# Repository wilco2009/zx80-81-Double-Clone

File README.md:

# PROJECT DOUBLE CLON ZX80/ZX81

Reading the works of [Grant Searle](http://searle.x10host.com/#ZX80), I have decided to start with the project to build a full computer to understand in depth his functionality. What can be more proper that a ZX80 totally based in discrete chips? 

In my spare time, I have started to work on it and you can find the results in the following lines.

I have copyied the schematics from the original zx80, and have made some modifications on it.

- I have added the extra circuitery to generate /NMI signal (Grant Searle Schematics), making possible to have two machines in one, by selecting it through a switch.
- Original 1K RAM in two chips have been replaced by one SRAM chip of  32KB.
- Original 4K ROM have been replaced by a EEPROM of 32KB. It necesary to store both ROMs (ZX80/ZX81) and it is cheaper than other smaller EPROMs.
-  RF modulator have been removed and replaced by a circuit to generate the standard back porch, missing in the original ZX80 PAL signal.

The final result is nor a exact copy of the original as the case of Grant, but the board match accurately in the original case, and I very happy with the result.

## TECHNICAL & ASSEMBLY INFORMATION

In this project you can find the necesary information to build your own zx80. I think the most funny way to obtain your clon is to do it from zero, but if you wanna a clon and need the PCB or you have not enough knowledge or experience to assembly it, I have some spare PCBs and componentes, and I can sell them or assembly the clon for you. Please feel free to contact me and I'm sure we can reach an agreenment. ;)

Current version: 1.1

![](https://lh3.googleusercontent.com/rCJV6tn4bRtD5xP2J01XtbQhOAFcQkIHwjG2PTs5kUFLTJYEPpwRD9dPU9Wus_7P2roRMrFiV_r6bx4AB1eH3hhHG4VBcHm-jtsIfwT51LC9u5qDKVhMcgAC-uYpSRKtiEv6ICVfqDUmrft0VXdILqsLhS6f-ci5W7Umk74fWQYKdmCltZMjROodQSZJIWuj3sWZtwkx2SUn3Zm80keVlYFTvZAvUO4RSQdXKRYVVGPSJaJdWytPF-uEiMIzvv5qfT4mYDBnC-GfqofApX20-UyLoEvZvTxQKA6cM-wEbGhz7QX-2P5Ngz30T_aOOOsLFDybzaFVSkEu0-Aztuu-lsrUIOo-5BsEfMnfYWue9epBj3OxYwocKKNFXdKxPxSTB5UOF6xXgVXRRxUQgXtDaMdEkAA_8DmF7i70zOS1lgH9-kZtPJs_eu8M_NfuGdDXssUw_kXJS4aPKvZ8_ZMPcppX3AiGHYtJN76VHx3QsB8ZefL5xlYTNOjEyXqZktvqzpaWWwEC28iiI7Rkx7_iQb64YHFRn1RQnPd6H6iP8zeCWNG2FOciLwMQ_T2f79s7PXthGdRW-6iFVxDD1xcBhBEmMfMiO6Gdjo2rIUpM3x4K8OVurMoqewDZ2G1iEkNCWaOpOh4981G3RFsP8XLy4C4ls8FTX44saukjyuqq=w845-h981-no)

## JUMPER POSITION
JP1: RAMOE, Not relevant but must be present in one position
JP2:
              1-2 - Inverse Video
              2-3 - Standard Video
S2: ZX80/81 Mode selection (If you use external selection from the expansion board this jumper have to be removed)
              1-2 - ZX81 mode
              2-3 - ZX80 mode.

S4: Function of the Pin23B in the expansion bus. 
In original ZX80 pin 23B of the expansion bus is spare, but in a ZX81 PIN23B is use as /ROMCS signal.
If you want to use external zx81 mode selection form the expansion board you have to use position 1-2. In this case (in zx81 mode) cards replacing the internal ROM will not works.
If you prefer to use this kind of cards, you have to wire the zx81 selector (S2) directly to an accesible switch and set S4 in 2-3 position (remember to remove JP1 in the expansion board)
              1-2 - ZX81/ZX80 mode selection in PIN 23B
              2-3 - /ROMOE in PIN 23B

### Back porch Grant Searle solution:

              JP3 = 2-3
              JP5 = OFF
              JP6 = 1-2

### Back porch generation José Leandro solution:
              Adjust image with R37 & R33
              JP3 = 1-2
              JP5 = ON
              JP6 = 2-3

### Without Backporch generation (original ZX80 video)
              JP3 = 1-2
              JP5 = OFF
              JP6 = 1-2
              
## EXPANSION BOARD

This board has double functionality, first leaves enough room to connect zx81 cards  without trip with the video connector, and by other hand adds some extra functionality to the main board.

Expansion board let you to supply power to the computer with a miniUSB charger. If you plan to use external cards using 9V you will must to connect the computer to a 9V PS through the standard conector.
If you use the miniUSB supply, you could use the ON/OFF switch present in the board (S1) to turn on the computer.
S2 is a reset button, and it will works in any case.
JP7 Lets you to select ZX80/81 mode from the board if the position of the main jumper S4 is 1-2 and JP1 in the expansion board is ON.

JP1 Lets you aisle pin23B in the computer from the JP7 selector. It must be OFF if computer jumper S4 is 2-3.

![Clon working together with the ZXBlast](https://lh3.googleusercontent.com/j9ALMYmShmvCE-jy-AzifAf2zu_0noKhuHjYqihIMtmODiZwof2czWIUYXH-UqWGO6TdXiLnMDjAKpj7Po1c5WaS6kIWaJdyXEqjynNArSz48OjEJksTGsXhDxQqEvnr6YDXmGl5VvESaMWlwIdJ6xjhwu2kQWZDYximzGeFjO39mOyrUMT1J-gvP3T8bGvWy7lPkWDsSiR0pI6hCDJZr2bOI1wuq31htQXp7wsT5vWe7ypyu1pTyPivk21z11Azjm-WXjnvVRQzJSwvq5q3OPzuYVv2PyCXvG03Tv6p_5taKzRV-rwySb_m_U9nDuxuRpI7Uc-8QEj6cFWM4ZI8NtL62JtfRc3yyowyizVgGyirSfv9Bk2rxOZqB-cOk6DNdtdGGdJT4QNYqnln8sdsbW3eD9JWjGkwFdYOPOAoj-ihRwhNHcHDzzXuyWnVDI54tBXznl0jK5OOICXLZPlEjcX42goKXJJ15L38fqvd_e-W1liQFMYBwjwnZQ0DPTSEEiSlLOfVQjilyQhW0fKNTQ-jeCu2VwTQkMloKwc0vevMCimGE85adegjdQxXJi_FQP6vlO9OII5GSUV8qNXudLEAzHOdmtRVcGPY-64G44qyDU0Gr9a-xIT18pK3NaAvpgWDecYkdOFkBCX6qmApyG_PxvDnz6c9Qs07RMNK=w1156-h981-no)

CONTACT: wilcoavs at gmail dot com

Update 01/02/2020.
Fix to resolve an incompatibility with some 74LS00s who inverts the screen. It is necessary to insert a 47K resistor between pin 1 and pin 14 of IC 11.

Update 17/02/2021 (many thanks to Augusto Baffa)
Quoted Augusto Baffa:
"My signal clock from IC18 PIN 9 was about (0-3v) and the High Pass Filter created by R25 and C11 was about (0-1v). It works on IC16 PIN 9 to generate the pulse that loads S/L on IC9 PIN 1 but was not working to load the latch'd on normal/inverse circuit 'cos IC11 pin 3 was always high.

So, after some testing I found that it's necessary to use another high pass filter to feed IC11 PIN2. I'm using a 100pF capacitor and a 3k6 resistor. After that it works fine. 

there is another item that could be improved. I've tested the Ear/cassete interface and it's producing a very low signal to IC10 PIN2.
 I analyzed the circuit on proteus and compared with original zx81 schematics and get the following:

Blue signal (it's dark... sorry)  is the signal produced by the original Searle's version. The red one is my propose in order to use the same PCB holes. and the green is the signal produced by the original zx81 circuit."

https://wilco2009.blogspot.com/2017/07/project-double-clon-zx80zx81-reading.html

## ACKNOLEDGEMENTS
- Jim Westwood - For designing the original machine
- Clive Sinclair - For introducing me in the computers world.
- Grant Searle - For his excellent work, he was the origin of mine. 
- Jose_Leandro, habbisoft - (in special way to jose_leandro) For helpping me in de debugging phase
- alvaroalea - For create an amaizing 3d printed case.
- carmeloco,flopping,sinclair200 - for supporting me in the initial phase

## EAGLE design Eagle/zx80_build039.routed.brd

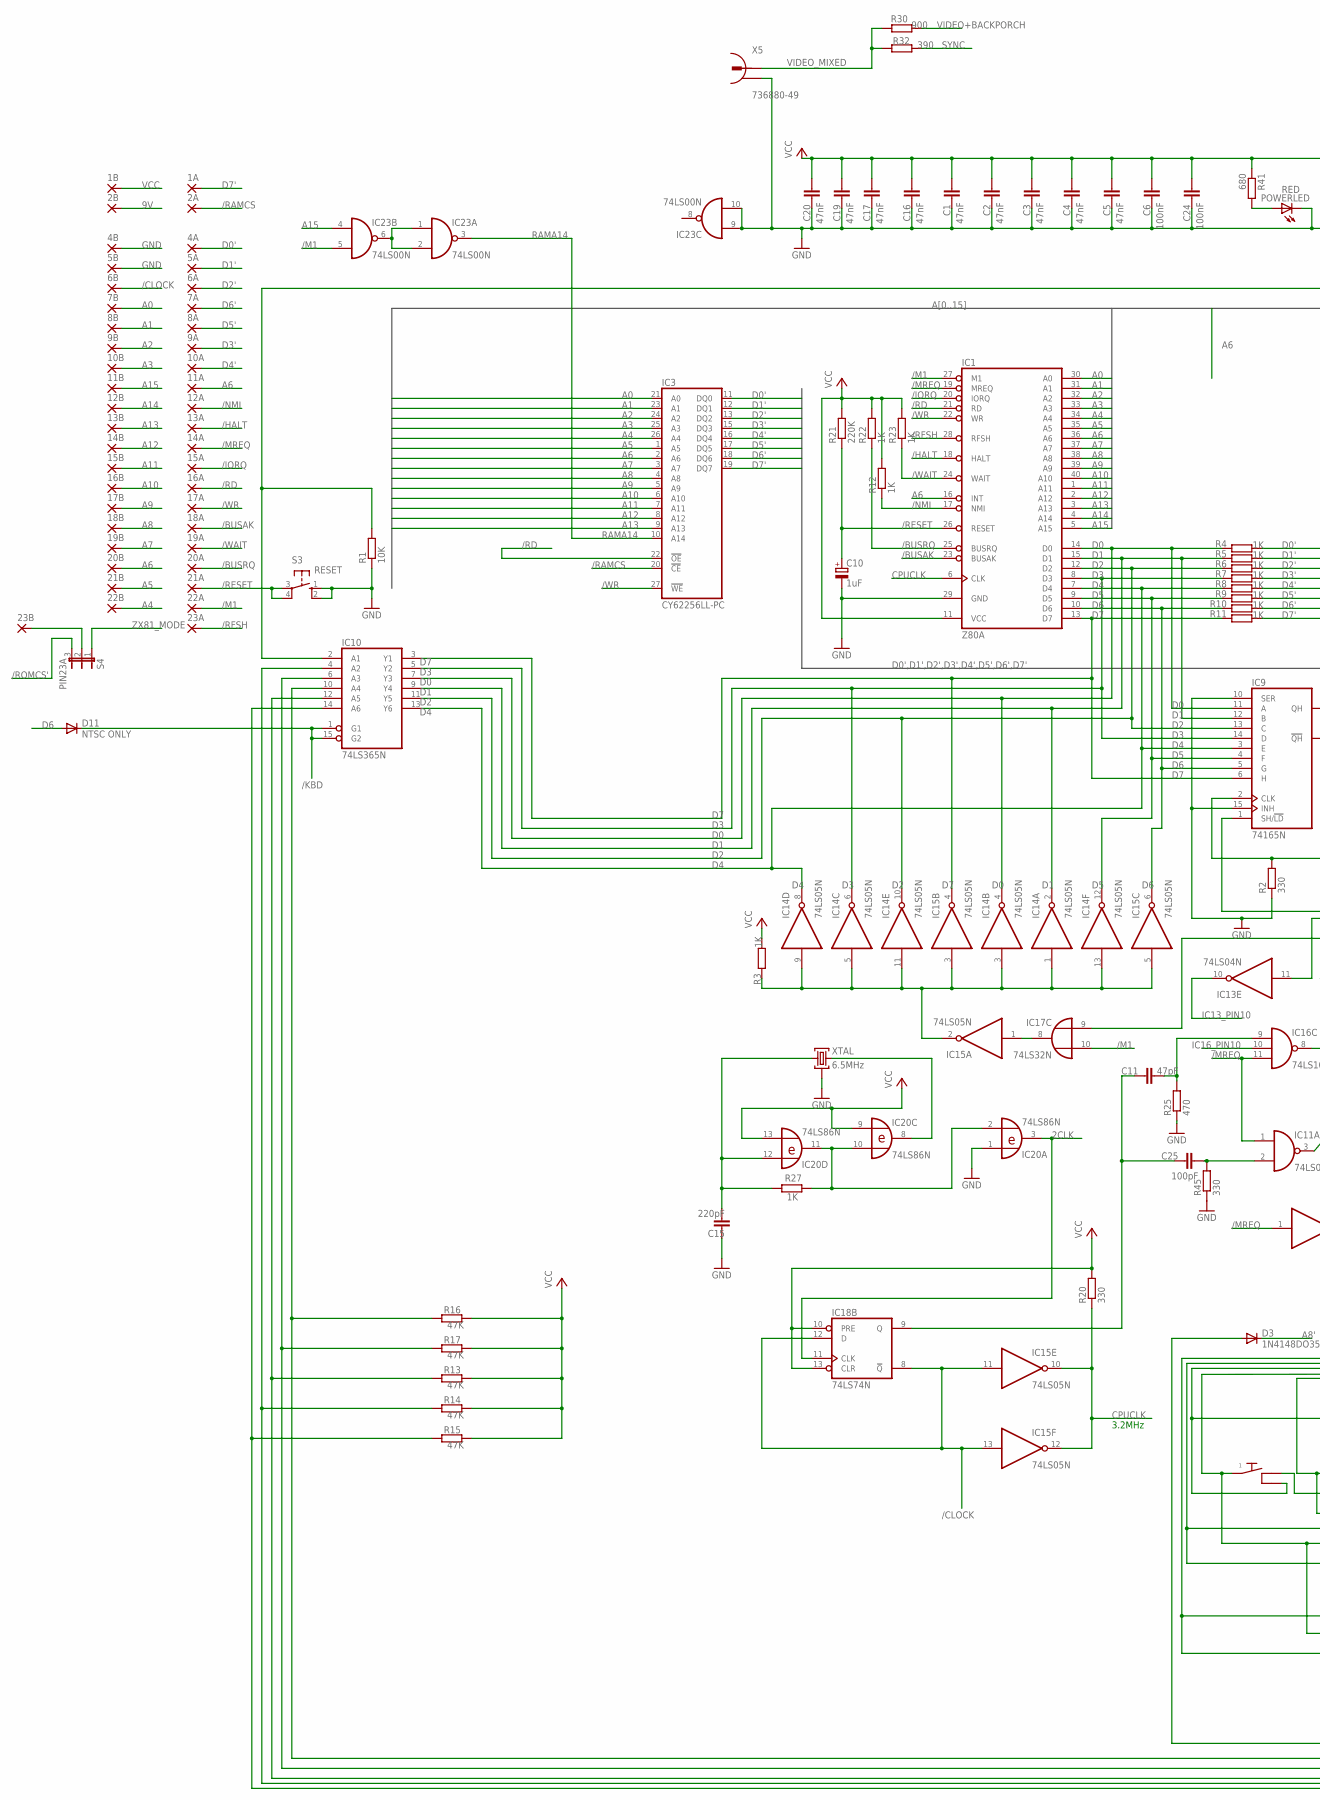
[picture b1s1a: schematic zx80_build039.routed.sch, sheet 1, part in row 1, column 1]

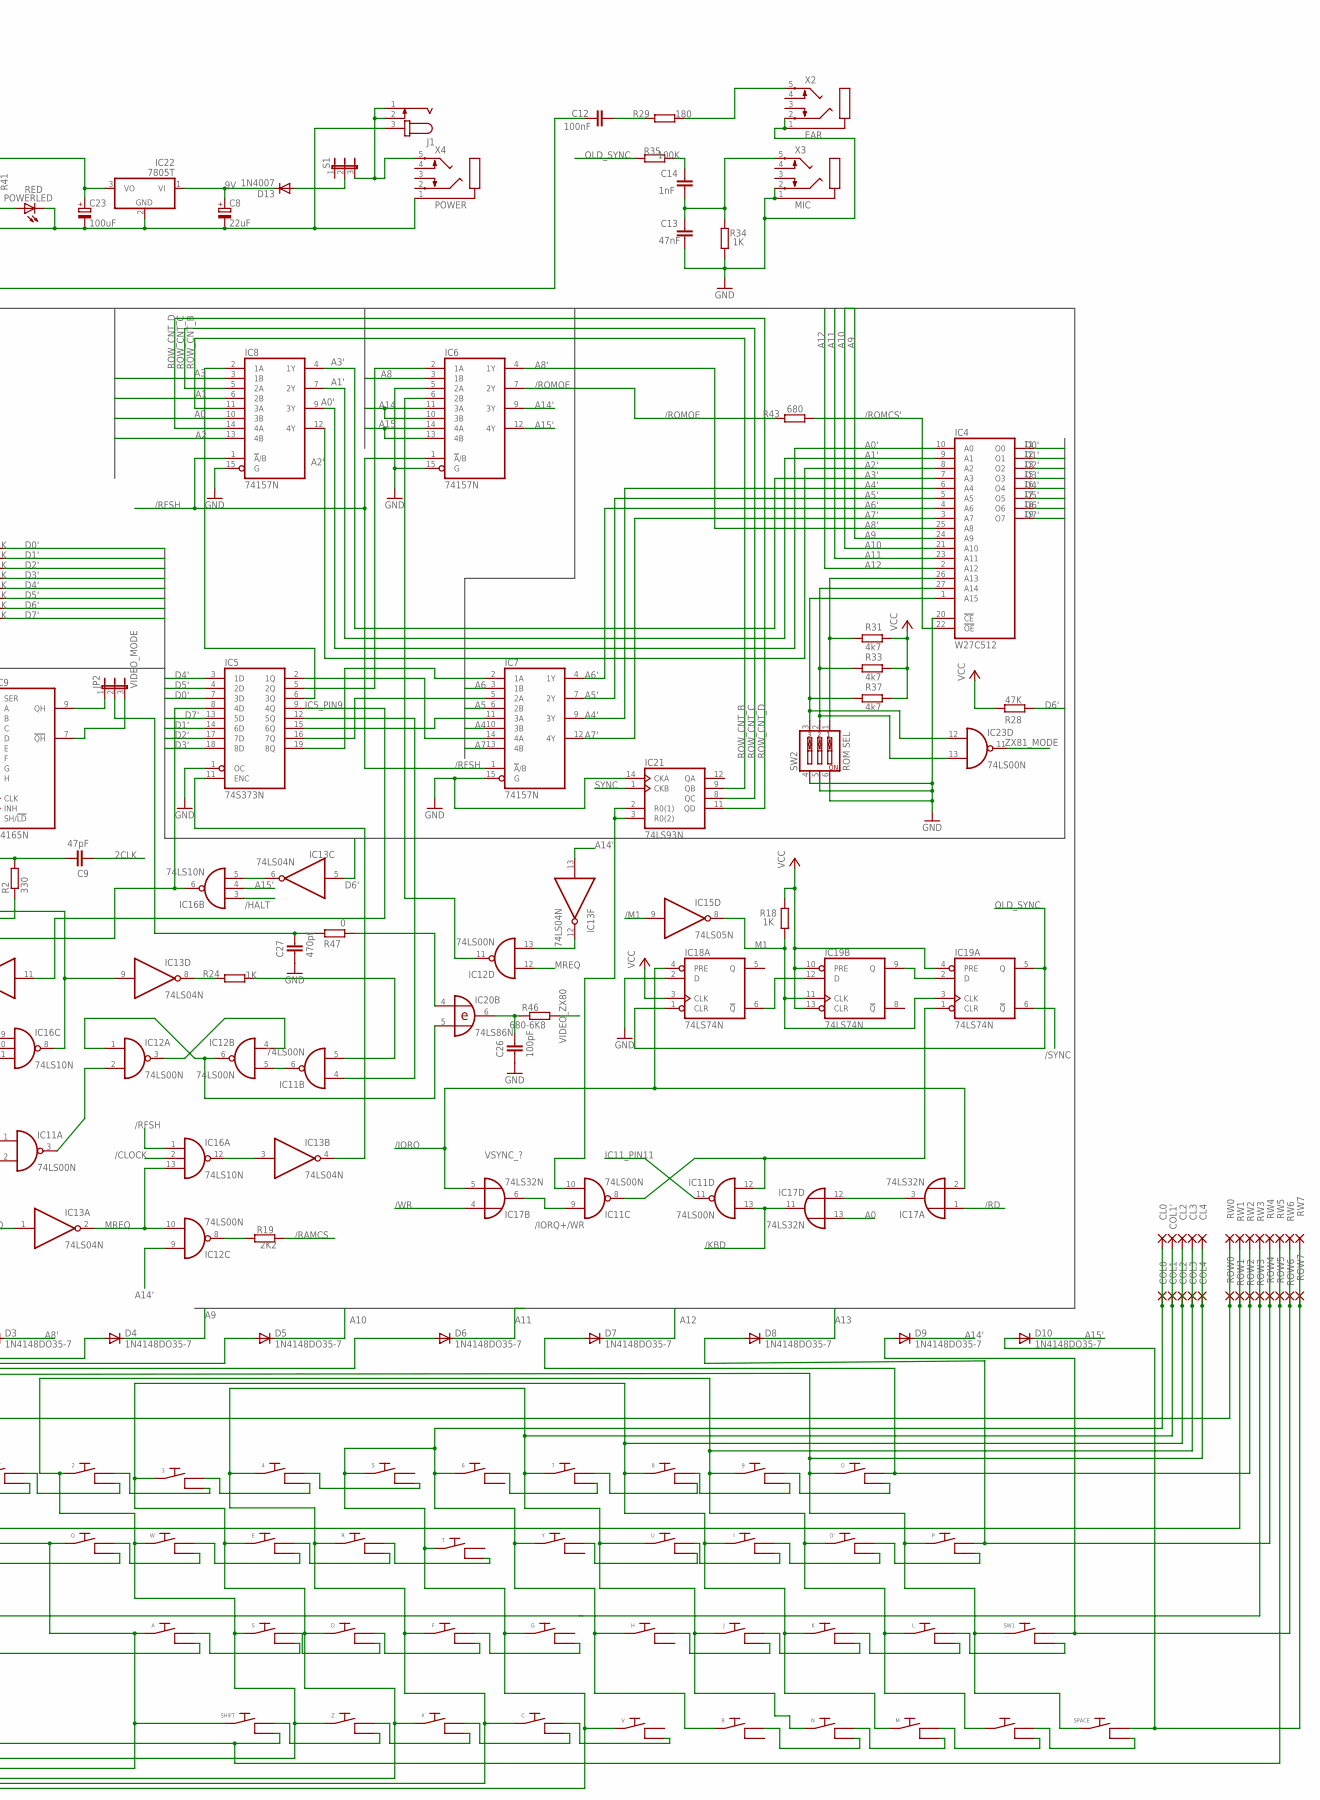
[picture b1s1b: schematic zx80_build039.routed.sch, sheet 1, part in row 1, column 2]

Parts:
1, 2, 3, 4, 5, 6, 7, 8, 9, .: TA_DK
1A, 1B, 2A, 2B, 4A, 4B, 5A, 5B, 6A, 6B, 7A, 7B, 8A, 8B, 9A, 9B, 10A, 10B, 11A, 11B, 12A, 12B, 13A, 13B, 14A, 14B, 15A, 15B, 16A, 16B, 17A, 17B, 18A, 18B, 19A, 19B, 20A, 20B, 21A, 21B, 22A, 22B, 23A, 23B: SMD2EDGEPIN; EDGEPIN
A: TA_DK
B: TA_DK
C: TA_DK
C1, C2, C3, C4, C5, C13, C16, C17, C19, C20: 47nF; C025-024X044
C6, C12: 100nF; C025-024X044
C8: 22uF; E2,5-5
C9: 47pF; C050-024X044
C10: 1uF; E2,5-5
C11: 47pF; C025-024X044
C14: 1nF; C025-024X044
C15: 220pF; C025-024X044
C23: 100uF; E2,5-5
C24: 100nF; C050-025X075
C25: 100pF; C025-024X044
C26: 100pF; C050-024X044
C27: 470pf; C050-024X044
CL0, CL2, CL3, CL4: 1,6/0,8
COL0, COL1, COL1', COL2, COL3, COL4: 1,6/0,8
D: TA_DK
D3, D4, D5, D6, D7, D8, D9, D10: 1N4148DO35-7; DO35-7
D11: NTSC ONLY; DO35-7
D13: 1N4007; DO41-10
E: TA_DK
F: TA_DK
G: TA_DK
H: TA_DK
I: TA_DK
IC1: Z80A; DIL40
IC3: CY62256LL-PC; DIL28-6
IC4: W27C512; DIL28
IC5: 74S373N; DIL20
IC6, IC7, IC8: 74157N; DIL16
IC9: 74165N; DIL16
IC10: 74LS365N; DIL16
IC11, IC12, IC23: 74LS00N; DIL14
IC13: 74LS04N; DIL14
IC14, IC15: 74LS05N; DIL14
IC16: 74LS10N; DIL14
IC17: 74LS32N; DIL14
IC18, IC19: 74LS74N; DIL14
IC20: 74LS86N; DIL14
IC21: 74LS93N; DIL14
IC22: 7805T; TO220H
J: TA_DK
J1: JACK-PLUG0; SPC4077
JP2: VIDEO_MODE; JP2
K: TA_DK
L: TA_DK
M: TA_DK
N: TA_DK
O: TA_DK
O': TA_DK
P: TA_DK
POWERLED: RED; LED3MM
Q: TA_DK
R: TA_DK
R1: 10K; 0204/7
R2, R20, R45: 330; 0204/7
R3, R4, R5, R6, R7, R8, R9, R10, R11, R12, R18, R22, R23, R24, R27, R34: 1K; 0204/7
R13, R14, R15, R16, R17, R28: 47K; 0204/7
R19: 2K2; 0204/7
R21: 220K; 0204/7
R25: 470; 0204/7
R29: 180; 0204/7
R30: 900; 0204/7
R31, R33, R37: 4k7; 0204/7
R32: 390; 0204/7
R35: 100K; 0204/7
R41, R43: 680; 0204/7
R46: 680-6K8; 0204/7
R47: 0; 0204/7
ROW0, ROW1, ROW2, ROW3, ROW4, ROW5, ROW6, ROW7: 1,6/0,8
RW0, RW1, RW2, RW3, RW4, RW5, RW6, RW7: 1,6/0,8
S: TA_DK
S1: JP2E; JP2
S3: RESET; B3F-10XX
S4: PIN23A; JP2
SHIFT: TA_DK
SPACE: TA_DK
SW1: TA_DK
SW2: ROM SEL; EDG-03
T: TA_DK
U: TA_DK
V: TA_DK
W: TA_DK
X: TA_DK
X2: EAR; PG203J
X3: MIC; PG203J
X4: POWER; PG203J
X5: 736880-49
XTAL: 6.5MHz; HC49U
Y: TA_DK
Z: TA_DK

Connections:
2CLK: C9.2, IC18.11 (CLK), IC20.3 (O)
9V: 2B.1, C8.+, D13.C, IC22.1 (VI)
/BUSAK: 18A.1, IC1.23 (BUSAK)
/BUSRQ: 20A.1, IC1.25 (BUSRQ), R22.1
/CLOCK: 6B.1, IC15.11 (I), IC15.13 (I), IC16.2 (I1), IC18.8 (!Q), IC18.12 (D); also elsewhere on the board
/HALT: 13A.1, IC1.18 (HALT), IC16.3 (I0); also elsewhere on the board
/IORQ: 15A.1, IC1.20 (IORQ), IC17.2 (I1), IC17.5 (I1), IC18.4 (PRE); also elsewhere on the board
/IORQ+/WR: IC11.9 (I0), IC17.6 (O); also elsewhere on the board
/KBD: D11.C, IC10.1 (G1), IC10.15 (G2), IC11.13 (I1), IC17.11 (O)
/M1: 22A.1, IC1.27 (M1), IC15.9 (I), IC17.10 (I1), IC23.5 (I1); also elsewhere on the board
/MREQ: 14A.1, IC1.19 (MREQ), IC11.1 (I0), IC13.1 (I), IC16.11 (I2)
/NMI: 12A.1, IC1.17 (NMI), R12.1; also elsewhere on the board
/RAMCS: 2A.1, IC3.20 (!CE), R19.1
/RD: 16A.1, IC1.21 (RD), IC3.22 (!OE), IC17.1 (I0)
/RESET: 21A.1, C10.+, IC1.26 (RESET), R21.1, S3.3, S3.4 (P1)
/RFSH: 23A.1, IC1.28 (RFSH), IC6.1 (!A!/B), IC7.1 (!A!/B), IC8.1 (!A!/B), IC16.1 (I0)
/ROMCS': IC4.22 (!OE), R43.1, S4.3
/ROMOE: IC6.7 (2Y), R43.2
/SYNC: IC19.6 (!Q)
/WAIT: 19A.1, IC1.24 (WAIT), R23.1; also elsewhere on the board
/WR: 17A.1, IC1.22 (WR), IC3.27 (!WE), IC17.4 (I0)
A0: 7B.1, IC1.30 (A0), IC3.21 (A0), IC8.10 (3B), IC17.13 (I1); also elsewhere on the board
A0': IC4.10 (A0), IC8.9 (3Y)
A1: 8B.1, IC1.31 (A1), IC3.23 (A1), IC8.6 (2B); also elsewhere on the board
A1': IC4.9 (A1), IC8.7 (2Y)
A2: 9B.1, IC1.32 (A2), IC3.24 (A2), IC8.13 (4B)
A2': IC4.8 (A2), IC8.12 (4Y)
A3: 10B.1, IC1.33 (A3), IC3.25 (A3), IC8.3 (1B)
A3': IC4.7 (A3), IC8.4 (1Y)
A4: 22B.1, IC1.34 (A4), IC3.26 (A4), IC7.10 (3B)
A4': IC4.6 (A4), IC7.9 (3Y)
A5: 21B.1, IC1.35 (A5), IC3.1 (A5), IC7.6 (2B)
A5': IC4.5 (A5), IC7.7 (2Y)
A6: 11A.1, 20B.1, IC1.16 (INT), IC1.36 (A6), IC3.2 (A6), IC7.3 (1B)
A6': IC4.4 (A6), IC7.4 (1Y)
A7: 19B.1, IC1.37 (A7), IC3.3 (A7), IC7.13 (4B)
A7': IC4.3 (A7), IC7.12 (4Y)
A8: 18B.1, IC1.38 (A8), IC3.4 (A8), IC6.3 (1B)
A8': D3.C, IC4.25 (A8), IC6.4 (1Y)
A9: 17B.1, D4.C, IC1.39 (A9), IC3.5 (A9), IC4.24 (A9)
A10: 16B.1, D5.C, IC1.40 (A10), IC3.6 (A10), IC4.21 (A10)
A11: 15B.1, D6.C, IC1.1 (A11), IC3.7 (A11), IC4.23 (A11)
A12: 14B.1, D7.C, IC1.2 (A12), IC3.8 (A12), IC4.2 (A12)
A13: 13B.1, D8.C, IC1.3 (A13), IC3.9 (A13)
A14: 12B.1, IC1.4 (A14), IC6.10 (3B), IC6.11 (3A)
A14': D9.C, IC6.9 (3Y), IC12.9 (I0), IC13.13 (I)
A15: 11B.1, IC1.5 (A15), IC6.13 (4B), IC6.14 (4A), IC23.4 (I0)
A15': D10.C, IC6.12 (4Y), IC16.4 (I1)
CPUCLK: IC1.6 (CLK), IC15.10 (O), IC15.12 (O), R20.1
D0: IC1.14 (D0), IC9.11 (A), IC10.7 (Y3), IC14.4 (O), R4.2
D0': 4A.1, IC3.11 (DQ0), IC4.11 (O0), IC5.7 (3D), R4.1
D1: IC1.15 (D1), IC9.12 (B), IC10.9 (Y4), IC14.2 (O), R5.2
D1': 5A.1, IC3.12 (DQ1), IC4.12 (O1), IC5.14 (6D), R5.1
D2: IC1.12 (D2), IC9.13 (C), IC10.11 (Y5), IC14.10 (O), R6.2
D2': 6A.1, IC3.13 (DQ2), IC4.13 (O2), IC5.17 (7D), R6.1
D3: IC1.8 (D3), IC9.14 (D), IC10.5 (Y2), IC14.6 (O), R7.2
D3': 9A.1, IC3.15 (DQ3), IC4.15 (O3), IC5.18 (8D), R7.1
D4: IC1.7 (D4), IC9.3 (E), IC10.13 (Y6), IC14.8 (O), R8.2
D4': 10A.1, IC3.16 (DQ4), IC4.16 (O4), IC5.3 (1D), R8.1
D5: IC1.9 (D5), IC9.4 (F), IC14.12 (O), R9.2
D5': 8A.1, IC3.17 (DQ5), IC4.17 (O5), IC5.4 (2D), R9.1
D6: D11.A, IC1.10 (D6), IC9.5 (G), IC15.6 (O), R10.2
D6': 7A.1, IC3.18 (DQ6), IC4.18 (O6), IC13.5 (I), R10.1, R28.1
D7: IC1.13 (D7), IC9.6 (H), IC10.3 (Y1), IC15.4 (O), R11.2
D7': 1A.1, IC3.19 (DQ7), IC4.19 (O7), IC5.13 (5D), R11.1
GND: 4B.1, 5B.1, C1.2, C2.2, C3.2, C4.2, C5.2, C6.2, C8.-, C10.-, C13.2, C15.1, C16.2, C17.2, C19.2, C20.2, C23.-, C24.2, C26.2, C27.2, IC1.29 (GND), IC3.14 (GND), IC4.14 (GND), IC4.20 (!CE), IC5.1 (OC), IC5.10 (GND), IC6.5 (2A), IC6.8 (GND), IC6.15 (G), IC7.8 (GND), IC7.15 (G), IC8.8 (GND), IC8.15 (G), IC9.8 (GND), IC9.10 (SER), IC9.15 (INH), IC10.8 (GND), IC11.7 (GND), IC12.7 (GND), IC13.7 (GND), IC14.7 (GND), IC15.7 (GND), IC16.7 (GND), IC17.7 (GND), IC18.2 (D), IC18.7 (GND), IC19.7 (GND), IC20.1 (I0), IC20.7 (GND), IC21.10 (GND), IC21.14 (CKA), IC22.2 (GND), IC23.7 (GND), IC23.9 (I0), IC23.10 (I1), J1.3, POWERLED.K (C), R1.1, R2.1, R25.1, R34.2, R45.1, S3.1 (S), S3.2 (S1), SW2.4, SW2.5, SW2.6, X2.1, X2.2, X3.1, X3.2, X4.1, X5.1 (2), XTAL.2; also elsewhere on the board
IC5_PIN9: IC5.9 (4Q), IC13.11 (I); also elsewhere on the board
IC11_PIN11: IC11.11 (O); also elsewhere on the board
IC12_PIN11: IC6.6 (2B), IC12.11 (O)
IC13_PIN10: IC13.10 (O)
IC16_PIN10: IC16.10 (I1); also elsewhere on the board
M1: IC15.8 (O), IC19.3 (CLK), IC19.11 (CLK), R18.2
MREQ: IC12.10 (I1), IC12.12 (I0), IC13.2 (O), IC16.13 (I2)
unnamed: IC5.5 (2Q), IC6.2 (1A)
unnamed: J1.1, J1.2, S1.3, X4.5
unnamed: IC5.6 (3Q), IC8.2 (1A)
unnamed: IC5.2 (1Q), IC7.14 (4A)
unnamed: POWERLED.A, R41.2
unnamed: C9.1, IC9.2 (CLK), R2.2
unnamed: IC14.1 (I), IC14.3 (I), IC14.5 (I), IC14.9 (I), IC14.11 (I), IC14.13 (I), IC15.2 (O), IC15.3 (I), IC15.5 (I), R3.2
unnamed: IC4.27 (A14), IC23.13 (I1), R33.1, SW2.2
unnamed: IC4.26 (A13), R31.1, SW2.1
unnamed: 4.1, 7.1, C.1, COL1.1, COL1'.1, F.1, IC10.4 (A2), J.1, N.1, R.1, R14.2, U.1
unnamed: IC13.6 (O), IC16.5 (I2)
unnamed: IC5.8 (4D), IC16.6 (O), IC17.9 (I0)
unnamed: R29.1, X2.5
unnamed: IC15.1 (I), IC17.8 (O)
unnamed: U.2@8 (2), Y.2@1 (2)
unnamed: D5.A, Q.2@8 (2), ROW1.1, RW1.1
unnamed: C11.2, IC16.9 (I0), R25.2
unnamed: IC9.1 (SH/!LD), IC13.9 (I), IC16.8 (O)
unnamed: D10.A, ROW7.1, RW7.1, SPACE.2@1 (2)
unnamed: IC13.8 (O), R24.2
unnamed: 2.2@1 (2), 3.2@8 (2)
unnamed: IC11.3 (O), IC12.2 (I1)
unnamed: IC12.1 (I0), IC12.6 (O), IC20.5 (I1)
unnamed: IC12.3 (O), IC12.4 (I0)
unnamed: IC11.6 (O), IC12.5 (I1)
unnamed: IC11.5 (I1), R24.1
unnamed: IC5.12 (5Q), IC11.4 (I0)
unnamed: IC9.9 (QH), JP2.1
unnamed: IC9.7 (!QH), JP2.3
unnamed: 3.2@1 (2), 4.2@8 (2)
unnamed: IC12.13 (I1), IC13.12 (O)
unnamed: IC18.6 (!Q), IC19.12 (D)
unnamed: IC19.2 (D), IC19.9 (Q)
unnamed: IC4.1 (A15), IC23.12 (I0), R37.1, SW2.3
unnamed: IC11.8 (O), IC11.12 (I0), IC19.1 (CLR)
unnamed: IC13.3 (I), IC16.12 (O)
unnamed: IC17.3 (O), IC17.12 (I0)
unnamed: IC5.11 (ENC), IC13.4 (O)
unnamed: D3.A, ROW5.1, RW5.1, SHIFT.2@8 (2)
unnamed: IC12.8 (O), R19.2
unnamed: A.2@8 (2), D4.A, ROW3.1, RW3.1
unnamed: IC20.2 (I1), IC20.10 (I1), IC20.11 (O), R27.2
unnamed: C15.2, IC20.12 (I0), R27.1, XTAL.1
unnamed: IC20.8 (O), XTAL.3
unnamed: C27.1, JP2.2, R47.2
unnamed: 5.1, 6.1, B.1, CL0.1, COL0.1, G.1, H.1, IC10.14 (A6), R15.2, T.1, V.1, Y.1
unnamed: C12.2, IC10.2 (A1), R1.2
unnamed: C12.1, R29.2
unnamed: D13.A, S1.2
unnamed: C13.1, C14.2, R34.1, X3.5
unnamed: 3.1, 8.1, CL2.1, COL2.1, D.1, E.1, I.1, IC10.12 (A5), K.1, M.1, R13.2, X.1
unnamed: C14.1, R35.1
unnamed: 4.2@1 (2), 5.2@8 (2)
unnamed: 23B.1, S4.2
unnamed: C11.1, C25.1, IC18.9 (Q)
unnamed: D7.A, O.2@1 (2), ROW2.1, RW2.1
unnamed: C26.1, IC20.6 (O), R46.2
unnamed: IC20.4 (I0), R47.1
unnamed: 1.2@8 (2), D6.A, ROW0.1, RW0.1
unnamed: 1.2@1 (2), 2.2@8 (2)
unnamed: E.2@8 (2), W.2@1 (2)
unnamed: K.2@1 (2), L.2@8 (2)
unnamed: C25.2, IC11.2 (I1), R45.2
unnamed: Q.2@1 (2), W.2@8 (2)
unnamed: I.2@1 (2), O'.2@8 (2)
unnamed: C.2@8 (2), X.2@1 (2)
unnamed: C.2@1 (2), V.2@8 (2)
unnamed: J.2@1 (2), K.2@8 (2)
unnamed: D8.A, P.2@1 (2), ROW4.1, RW4.1
unnamed: H.2@1 (2), J.2@8 (2)
unnamed: A.2@1 (2), S.2@8 (2)
unnamed: I.2@8 (2), U.2@1 (2)
unnamed: D9.A, ROW6.1, RW6.1, SW1.2@1 (2)
unnamed: L.2@1 (2), SW1.2@8 (2)
unnamed: O'.2@1 (2), P.2@8 (2)
unnamed: 9.2@1 (2), O.2@8 (2)
unnamed: X.2@8 (2), Z.2@1 (2)
unnamed: ..2@1 (2), SPACE.2@8 (2)
unnamed: ..2@8 (2), M.2@1 (2)
unnamed: M.2@8 (2), N.2@1 (2)
unnamed: B.2@1 (2), N.2@8 (2)
unnamed: D.2@8 (2), S.2@1 (2)
unnamed: SHIFT.2@1 (2), Z.2@8 (2)
unnamed: D.2@1 (2), F.2@8 (2)
unnamed: F.2@1 (2), G.2@8 (2)
unnamed: E.2@1 (2), R.2@8 (2)
unnamed: R.2@1 (2), T.2@8 (2)
unnamed: 2.1, 9.1, ..1, CL3.1, COL3.1, IC10.10 (A4), L.1, O'.1, R16.2, S.1, W.1, Z.1
unnamed: 1.1, A.1, CL4.1, COL4.1, IC10.6 (A3), O.1, P.1, Q.1, R17.2, SHIFT.1, SPACE.1, SW1.1
unnamed: IC5.15 (6Q), IC7.11 (3A)
unnamed: IC5.16 (7Q), IC7.5 (2A)
unnamed: IC5.19 (8Q), IC7.2 (1A)
unnamed: IC23.1 (I0), IC23.2 (I1), IC23.6 (O)
unnamed: 6.2@1 (2), 7.2@8 (2)
unnamed: 7.2@1 (2), 8.2@8 (2)
unnamed: 8.2@1 (2), 9.2@8 (2)
OLD_SYNC: IC18.1 (CLR), IC19.5 (Q), R35.2
RAMA14: IC3.10 (A14), IC23.3 (O)
ROW_CNT_B: IC8.11 (3A), IC21.9 (QB)
ROW_CNT_C: IC8.5 (2A), IC21.8 (QC)
ROW_CNT_D: IC8.14 (4A), IC21.11 (QD)
SYNC: IC21.1 (CKB), R32.1; also elsewhere on the board
VCC: 1B.1, C1.1, C2.1, C3.1, C4.1, C5.1, C6.1, C16.1, C17.1, C19.1, C20.1, C23.+, C24.1, IC1.11 (VCC), IC3.28 (VCC), IC4.28 (VCC), IC5.20 (VCC), IC6.16 (VCC), IC7.16 (VCC), IC8.16 (VCC), IC9.16 (VCC), IC10.16 (VCC), IC11.14 (VCC), IC12.14 (VCC), IC13.14 (VCC), IC14.14 (VCC), IC15.14 (VCC), IC16.14 (VCC), IC17.14 (VCC), IC18.3 (CLK), IC18.10 (PRE), IC18.13 (CLR), IC18.14 (VCC), IC19.4 (PRE), IC19.10 (PRE), IC19.13 (CLR), IC19.14 (VCC), IC20.9 (I0), IC20.13 (I1), IC20.14 (VCC), IC21.5 (VCC), IC22.3 (VO), IC23.14 (VCC), R3.1, R12.2, R13.1, R14.1, R15.1, R16.1, R17.1, R18.1, R20.2, R21.2, R22.2, R23.2, R28.2, R31.2, R33.2, R37.2, R41.1; also elsewhere on the board
VIDEO+BACKPORCH: R30.1; also elsewhere on the board
VIDEO_MIXED: R30.2, R32.2, X5.2 (1)
VIDEO_ZX80: R46.1; also elsewhere on the board
VSYNC_?: IC11.10 (I1), IC21.2 (R0(1)), IC21.3 (R0(2)); also elsewhere on the board
ZX81_MODE: IC23.11 (O), S4.1; also elsewhere on the board

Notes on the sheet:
3.2MHz

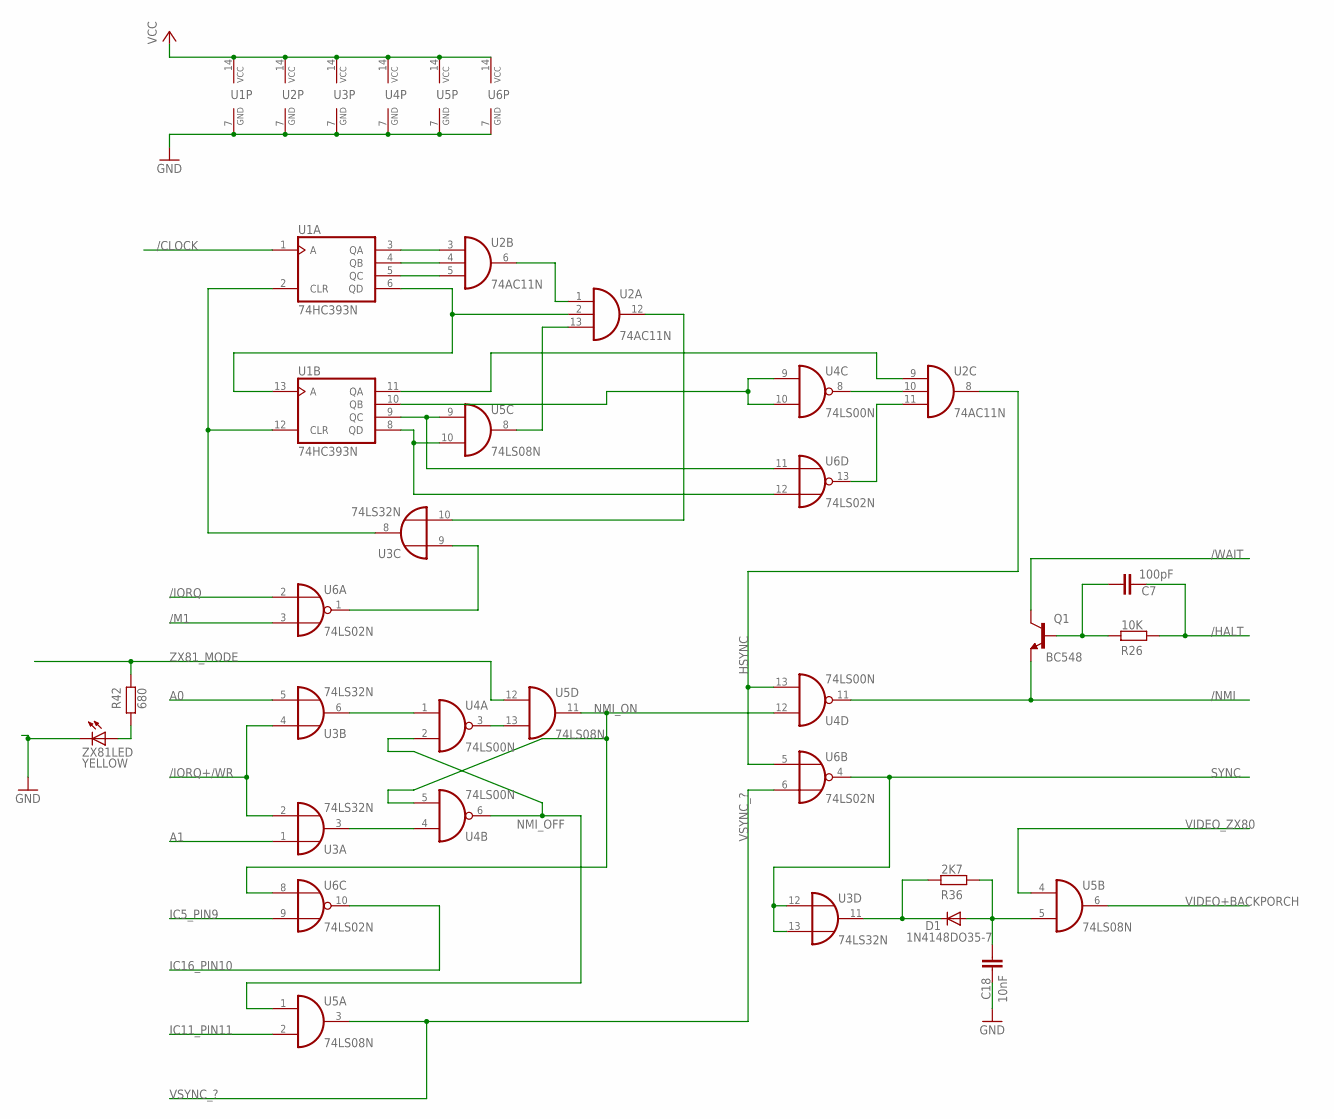
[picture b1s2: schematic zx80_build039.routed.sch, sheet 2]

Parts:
C7: 100pF; C025-024X044
C18: 10nF; C025-024X044
D1: 1N4148DO35-7; DO35-7
Q1: BC548; TO92-EBC
R26: 10K; 0204/7
R36: 2K7; 0204/7
R42: 680; 0204/7
U1: 74HC393N; DIL14
U2: 74AC11N; DIL14
U3: 74LS32N; DIL14
U4: 74LS00N; DIL14
U5: 74LS08N; DIL14
U6: 74LS02N; DIL14
ZX81LED: YELLOW; LED3MM

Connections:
/CLOCK: U1.1 (A); also elsewhere on the board
/HALT: C7.2, R26.1; also elsewhere on the board
/IORQ: U6.2 (I0); also elsewhere on the board
/IORQ+/WR: U3.2 (I1), U3.4 (I0); also elsewhere on the board
/M1: U6.3 (I1); also elsewhere on the board
/NMI: Q1.E, U4.11 (O); also elsewhere on the board
/WAIT: Q1.C; also elsewhere on the board
A0: U3.5 (I1); also elsewhere on the board
A1: U3.1 (I0); also elsewhere on the board
GND: C18.2, U1.7 (GND), U2.7 (GND), U3.7 (GND), U4.7 (GND), U5.7 (GND), U6.7 (GND), ZX81LED.K (C); also elsewhere on the board
HSYNC: U2.8 (O), U4.13 (I1), U6.5 (I0)
IC5_PIN9: U6.9 (I1); also elsewhere on the board
IC11_PIN11: U5.2 (I1); also elsewhere on the board
IC16_PIN10: U6.10 (O); also elsewhere on the board
unnamed: U3.9 (I0), U6.1 (O)
unnamed: C7.1, Q1.B, R26.2
unnamed: U1.3 (QA), U2.3 (I0)
unnamed: U1.4 (QB), U2.4 (I1)
unnamed: U1.5 (QC), U2.5 (I2)
unnamed: U2.1 (I0), U2.6 (O)
unnamed: U1.6 (QD), U1.13 (A), U2.2 (I1)
unnamed: U1.8 (QD), U5.10 (I1), U6.12 (I1)
unnamed: U1.10 (QB), U4.9 (I0), U4.10 (I1)
unnamed: U2.13 (I2), U5.8 (O)
unnamed: U2.12 (O), U3.10 (I1)
unnamed: U1.9 (QC), U5.9 (I0), U6.11 (I0)
unnamed: U1.11 (QA), U2.9 (I0)
unnamed: U1.2 (CLR), U1.12 (CLR), U3.8 (O)
unnamed: U2.10 (I1), U4.8 (O)
unnamed: U2.11 (I2), U6.13 (O)
unnamed: D1.C, R36.2, U3.11 (O)
unnamed: C18.1, D1.A, R36.1, U5.5 (I1)
unnamed: R42.1, ZX81LED.A
unnamed: U3.6 (O), U4.1 (I0)
unnamed: U3.3 (O), U4.4 (I0)
unnamed: U4.3 (O), U5.13 (I1)
NMI_OFF: U4.2 (I1), U4.6 (O), U5.1 (I0)
NMI_ON: U4.5 (I1), U4.12 (I0), U5.11 (O), U6.8 (I0)
SYNC: U3.12 (I0), U3.13 (I1), U6.4 (O); also elsewhere on the board
VCC: U1.14 (VCC), U2.14 (VCC), U3.14 (VCC), U4.14 (VCC), U5.14 (VCC), U6.14 (VCC); also elsewhere on the board
VIDEO+BACKPORCH: U5.6 (O); also elsewhere on the board
VIDEO_ZX80: U5.4 (I0); also elsewhere on the board
VSYNC_?: U5.3 (O), U6.6 (I1); also elsewhere on the board
ZX81_MODE: R42.2, U5.12 (I0); also elsewhere on the board

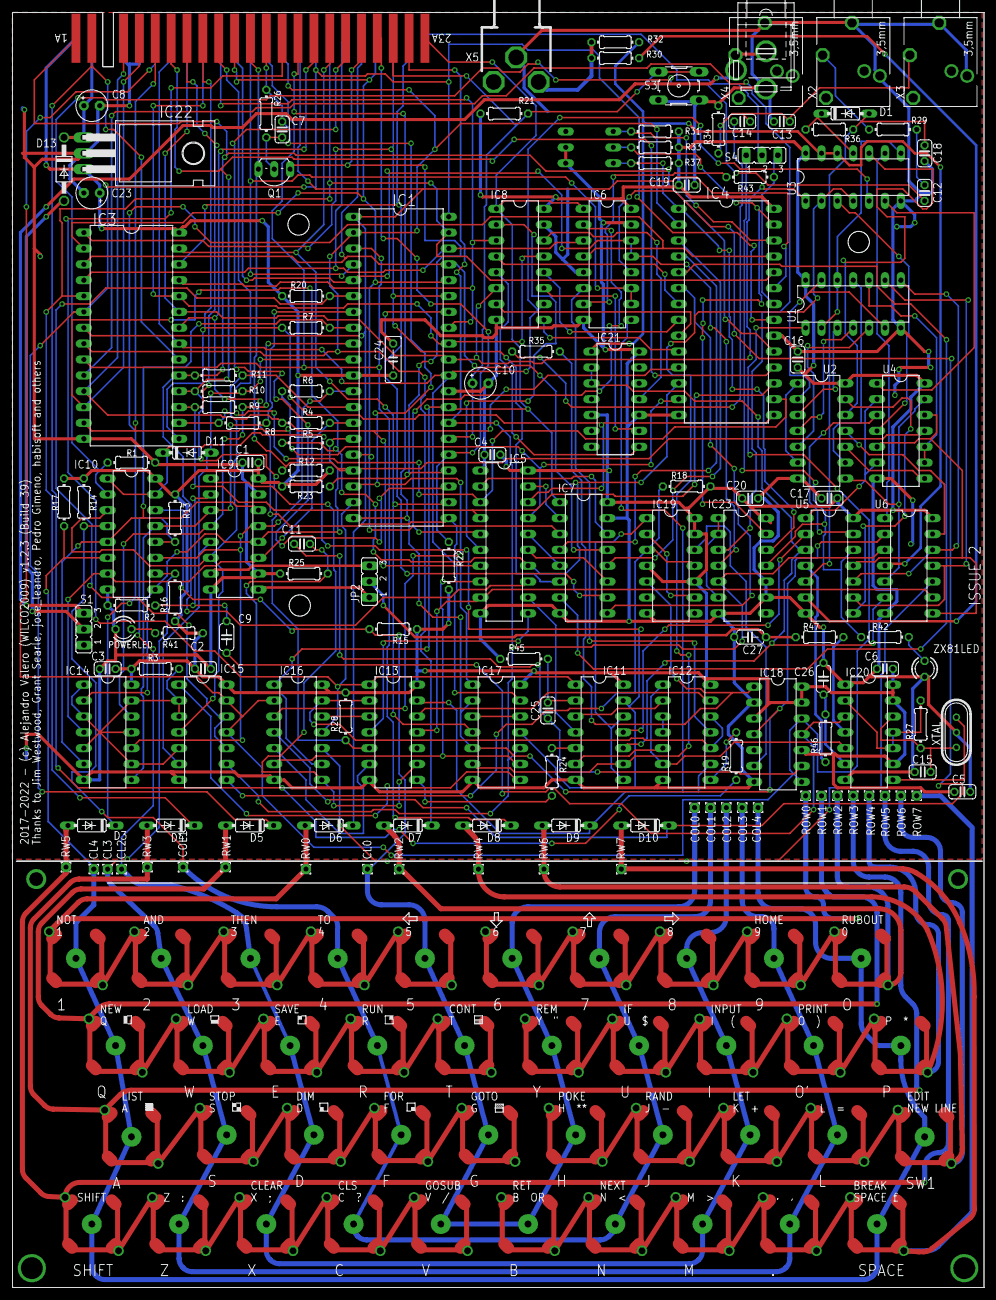
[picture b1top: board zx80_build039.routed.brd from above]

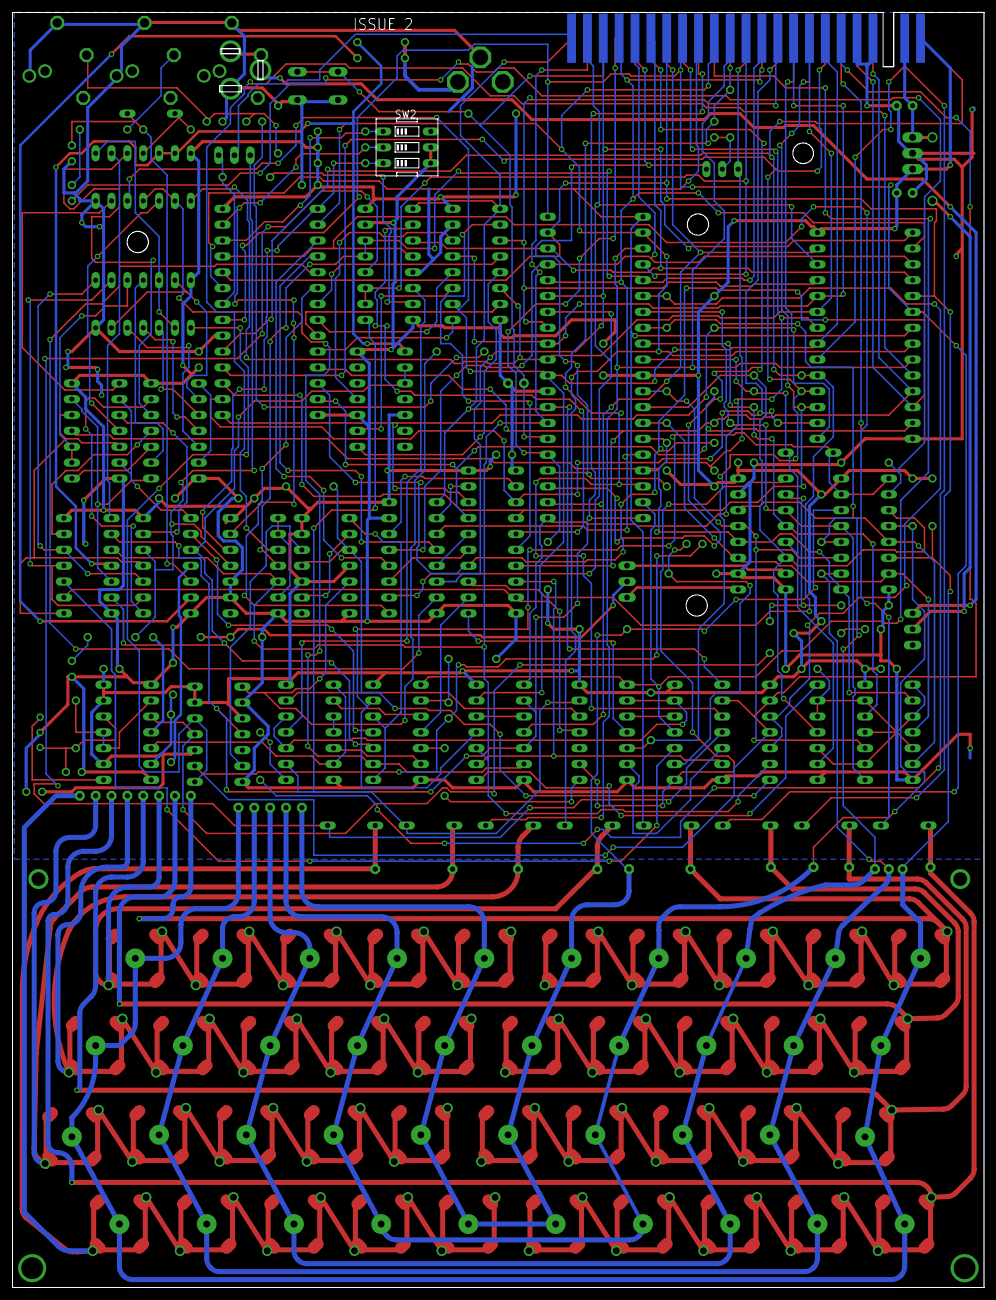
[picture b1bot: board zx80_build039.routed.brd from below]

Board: 2 copper layers, 155.6 x 204.2 mm, 231 parts (23 on the bottom side), 204 nets.

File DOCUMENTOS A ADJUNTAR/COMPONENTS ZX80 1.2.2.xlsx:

Part |  | Value | Device | Package
C1..C5,C13,C16,C17,C19,C20 | 10 | 47nF | capacitor
C6,C12,C24 | 3 | 100nF | capacitor
C7,C25,C26 | 3 | 100pF | capacitor
C8 | 1 | 22uF | capacitor
C9,C11 | 2 | 47pF | capacitor
C14 | 1 | 1nF | capacitor
C10 | 1 | 1uF | capacitor
C15 | 1 | 220pF | capacitor
C18 | 1 | 10nF | capacitor
C23 | 1 | 100uF | capacitor
C27 | 1 | 470pf | capacitor
D1..D11 | 11 | 1N4148 | diode
D13 | 1 | 1N4007 | diode
IC1 | 1 | Z80A | CPU | DIP40
IC3 | 1 | 62256 | RAM | DIP28
IC4 | 1 | W27C512 | EEPROM | DIP28
IC5 | 1 | 74LS373N | 74xx | DIP20
IC6..IC8 | 3 | 74LS157N | 74xx | DIP16
IC9 | 1 | 74165N | 74xx | DIP16
IC10 | 1 | 74LS365N | 74xx | DIP16
IC11,IC12,IC23,U4 | 4 | 74LS00N | 74xx | DIP14
IC13 | 1 | 74LS04 | 74xx | DIP14
IC14,IC15 | 2 | 74LS05N | 74xx | DIP14
IC16 | 1 | 74LS10 | 74xx | DIP14
IC17,U3 | 2 | 74LS32N | 74xx | DIP14
IC18,IC19 | 2 | 74LS74N | 74xx | DIP14
IC20 | 1 | 74LS86N | 74xx | DIP14
IC21 | 1 | 74LS93N | 74xx | DIP14
IC23 | 1 | 7805 | 5V regulator | TO220
U1 | 1 | 74LS393N | 74xx | DIP14
U2 | 1 | 74LS11N | 74xx | DIP14
U5 | 1 | 74LS08N | 74xx | DIP14
U6 | 1 | 74LS02N | 74xx | DIP14
POWERLED | 1 | LED | RED | 3MM
ZX81LED | 1 | LED | BLUE | 3MM
Q1 | 1 | BC548 | transistor-npn | TO92
R1,R26 | 2 | 10K | resistor | 0204/7
R20 | 1 | 330R | resistor | 0204/7
R3..R12,R18,R22..R24,R27,R34 | 16 | 1K | resistor | 0204/7
R13..R17,R28, | 6 | 47K | resistor | 0204/7
R19 | 1 | 2K2 | resistor | 0204/7
R21 | 1 | 220K | resistor | 0204/7
R29 | 1 | 180R | resistor | 0204/7
R31,R33,R37 | 3 | 4K7 | resistor | 0204/7
R35 | 1 | 100K | resistor | 0204/7
R41..R43 | 3 | 680R | resistor | 0204/7
R47 | 1 | 0R | resistor | 0204/7
X2,X3,X4 | 3 | PG203J | FEMALE JACK | 3.5MM
JP2 | 1 | JUMPER | VIDEO_MODE
S1 | 1 | SWITCH | POWER SW
S3 | 1 | PUSH BUTTON | RESET
S4 | 1 | JUMPER | PIN23A
SW2 | 1 | DIPSWITCH-3 | ROM SEL
X5 | 1 | 736880-49 | VIDEO CONN
XTAL | 1 | 6.5MHZ | CRYSTAL
VARIABLE VALUES |  | DEFAULT | ADJUSTED
R2 |  | 330R
R25 |  | 470R
R45 |  | 470R
R46 |  | 680R
R47 |  | 680R
R30 |  | 1K
R32 |  | 330R
R36 |  | 2K7

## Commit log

2023-03-29 added GERBER files
2023-07-17 build 039
